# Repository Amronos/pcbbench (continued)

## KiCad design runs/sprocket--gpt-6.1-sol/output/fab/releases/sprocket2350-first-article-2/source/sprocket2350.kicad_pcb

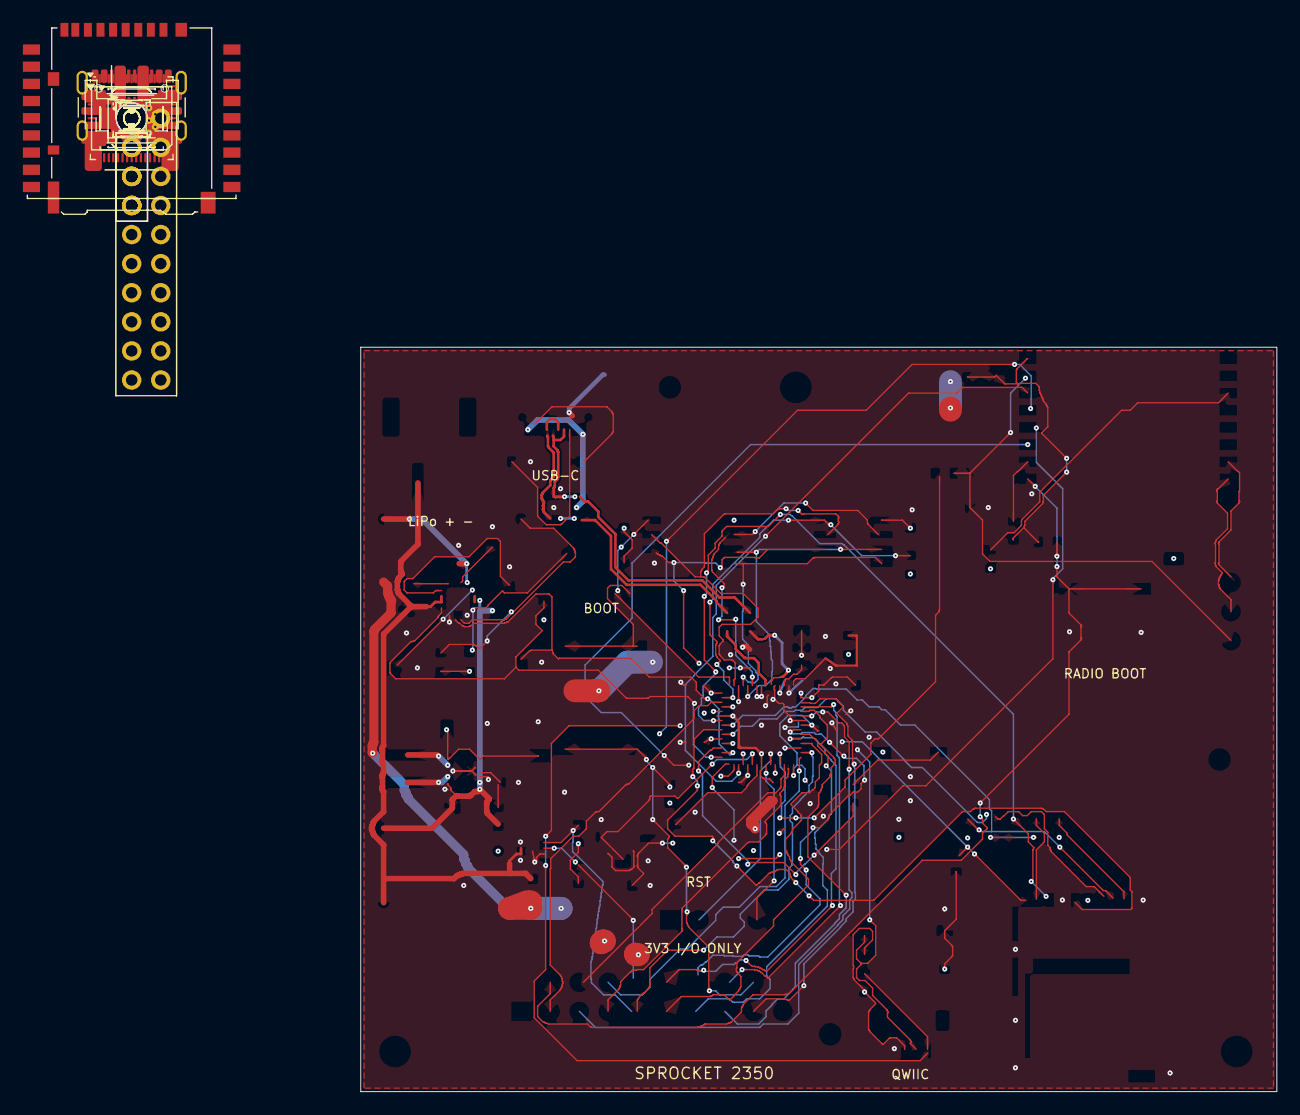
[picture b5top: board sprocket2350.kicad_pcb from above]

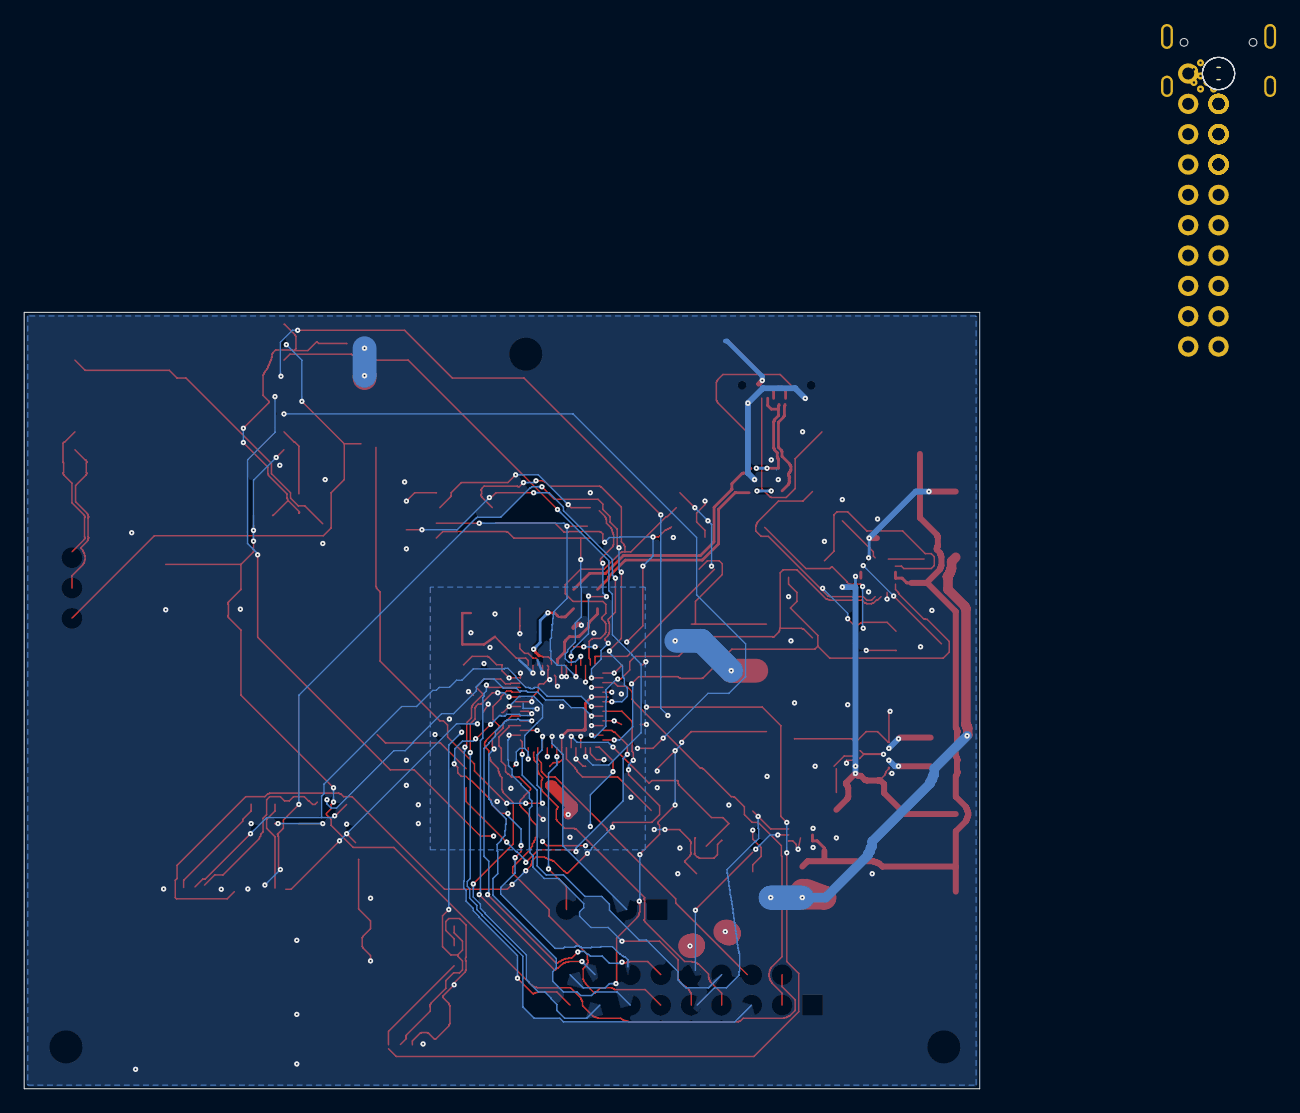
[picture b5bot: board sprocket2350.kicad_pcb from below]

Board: 4 copper layers, 80.0 x 65.0 mm, 106 parts (2 on the bottom side), 75 nets.

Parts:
C1, C2, C9, C10, C11, C12, C13, C14, C15, C16, C17, C18, C19, C25, C28, C31, C34, C35: 100 nF; C_0603_1608Metric
C3, C4: 15 pF; C_0603_1608Metric
C5, C7, C8: 4.7 µF; C_0805_2012Metric
C6: 22 µF; C_0603_1608Metric
C20: 100 nF; C_0201_0603Metric
C21, C29: 1 µF; C_0603_1608Metric
C22, C23, C24, C30, C33: 10 µF; C_0805_2012Metric
C26, C27, C32: 22 µF; C_1206_3216Metric
D1: RGB V6; LED_WS2812B_PLCC4_5.0x5.0mm_P3.2mm
FID1, FID2, FID3: Fiducial; Fiducial_1mm_Mask2mm
H1, H2, H3: M2.5; MountingHole_2.7mm_M2.5
J1: USB-C; USB_C_Receptacle_GCT_USB4105-xx-A_16P_TopMnt_Horizontal
J2: LiPo; JST_PH_S2B-PH-SM4-TB_1x02-1MP_P2.00mm_Horizontal
J3: Radio UART; PinHeader_1x04_P2.54mm_Vertical
J4: microSD; microSD_HC_Hirose_DM3AT-SF-PEJM5
J5: Qwiic / STEMMA QT; JST_SH_BM04B-SRSS-TB_1x04-1MP_P1.00mm_Vertical
J6: GPIO; PinHeader_2x10_P2.54mm_Vertical
J7: SWD; PinHeader_1x04_P2.54mm_Vertical
L1: 3.3 µH; L_Abracon_AOTA-B201610S
L2: 2.2 µH; L_Coilcraft_XxL4020
R1, R4, R13, R16, R17, R18, R19, R23, R24, R25, R26, R27, R28, R29, R30, R31: 10 kΩ; R_0603_1608Metric
R2: 1.8 kΩ; R_0603_1608Metric
R3, R5, R35: 1 kΩ; R_0603_1608Metric
R6: 33 Ω; R_0603_1608Metric
R7, R8, R32, R33: 5.1 kΩ; R_0603_1608Metric
R9, R10: 27 Ω; R_0603_1608Metric
R11: 8.66 kΩ; R_0603_1608Metric
R12: 3.48 kΩ; R_0603_1608Metric
R14: 68.1 kΩ; R_0603_1608Metric
R20, R21: 3.3 kΩ; R_0603_1608Metric
R22: 100 kΩ; R_0603_1608Metric
R34: 330 Ω; R_0603_1608Metric
R36: 100 Ω; R_0603_1608Metric
SW1: BOOT; SW_SPST_TL3342
SW2: RESET; SW_SPST_TL3342
SW3: RADIO BOOT; SW_SPST_TL3342
TP1: VBUS; TestPoint_Pad_D1.0mm
TP2: SYS; TestPoint_Pad_D1.0mm
TP3: +3V3; TestPoint_Pad_D1.0mm
TP4: GND; TestPoint_Pad_D1.0mm
TP5: BAT; TestPoint_Pad_D1.0mm
TP6: CHG_N; TestPoint_Pad_D1.0mm
TP7: USB_PGOOD_N; TestPoint_Pad_D1.0mm
TP8: CORE_1V1; TestPoint_Pad_D1.0mm
U1: RP2350A; QFN-60-1EP_7x7mm_P0.4mm_EP3.4x3.4mm
U2: 16 MB flash; SOIC-8_5.3x5.3mm_P1.27mm
U3: 8 MB PSRAM; SOIC-8_3.9x4.9mm_P1.27mm
U4: USB ESD; SOT-23-6
U5: Power-path charger; VQFN-16-1EP_3x3mm_P0.5mm_EP1.6x1.6mm
U6: 3.3 V buck-boost; Texas_DRC0010J
U7: Wi-Fi + BLE; ESP32-C3-WROOM-02
U8: Battery voltage / SOC; TDFN-8-1EP_2x2mm_P0.5mm_EP0.8x1.2mm
Y1: 12 MHz; Crystal_SMD_3225-4Pin_3.2x2.5mm

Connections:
/+3V3: C1.1, C2.1, C6.1, C9.1, C10.1, C11.1, C12.1, C13.1, C14.1, C15.1, C16.1, C17.1, C26.1, C27.1, C30.1, C31.1, C32.1, C33.1, C34.1, C35.1, D1.1 (VDD), J4.4 (VDD), J5.2, J6.1, J6.19, J7.1, R1.1, R2.1, R4.1, R6.1, R17.1, R18.1, R19.1, R20.1, R21.1, R23.1, R24.1, R25.1, R26.1, R27.1, R28.1, R29.1, R30.1, R31.1, R32.1, R33.1, TP3.1 (1_1), U1.1 (IOVDD), U1.11 (IOVDD), U1.20 (IOVDD), U1.30 (IOVDD), U1.38 (IOVDD), U1.44 (ADC_AVDD), U1.45 (IOVDD), U1.49 (VREG_VIN), U1.53 (USB_OTP_VDD), U1.54 (QSPI_IOVDD), U2.8 (VCC), U3.8 (VDD), U6.1 (VOUT), U6.10 (FB), U7.1 (3V3)
/ADC0: J6.5, U1.40 (GPIO26/ADC0)
/ADC1: J6.15, U1.41 (GPIO27/ADC1)
/ADC2: J6.16, U1.42 (GPIO28/ADC2)
/ADC3: J6.17, U1.43 (GPIO29/ADC3)
/BAT: C22.1, C28.1, J2.2, TP5.1 (1_1), U5.2 (BAT), U5.3 (BAT), U8.2 (CELL), U8.3 (VDD)
/BAT_TS: R13.1, U5.1 (TS)
/BOOT_SWITCH: R3.2, SW1.1
/BUCK_L1: L2.1, U6.4 (L1)
/BUCK_L2: L2.2, U6.2 (L2)
/BUCK_VINA: C25.1, R36.2, U6.8 (VINA)
/CC1: J1.A5 (CC1), R7.1
/CC2: J1.B5 (CC2), R8.1
/CHARGE_DISABLE: R17.2, U1.15 (GPIO11), U5.4 (~CE)
/CHG_ILIM: R12.1, U5.12 (ILIM)
/CHG_ISET: R11.1, U5.16 (ISET)
/CHG_N: R19.2, TP6.1 (1_1), U5.9 (~CHG)
/CHG_TMR: R14.1, U5.14 (TMR)
/CORE_1V1: C7.1, C8.1, C18.1, C19.1, C20.1, L1.1, TP8.1 (1_1), U1.6 (DVDD), U1.23 (DVDD), U1.39 (DVDD), U1.50 (VREG_FB)
/FLASH_CS: R1.2, R3.1, U1.60 (~QSPI_SS), U2.1 (~CS)
/GAUGE_SCL: J6.10, R21.2, U1.33 (GPIO21), U8.7 (SCL)
/GAUGE_SDA: J6.9, R20.2, U1.32 (GPIO20), U8.8 (SDA)
/GND: C1.2, C2.2, C3.2, C4.2, C5.2, C6.2, C7.2, C8.2, C9.2, C10.2, C11.2, C12.2, C13.2, C14.2, C15.2, C16.2, C17.2, C18.2, C19.2, C20.2, C21.2, C22.2, C23.2, C24.2, C25.2, C26.2, C27.2, C28.2, C29.2, C30.2, C31.2, C32.2, C33.2, C34.2, C35.2, D1.3 (VSS), J1.A1 (GND), J1.A12 (GND), J1.B1 (GND), J1.B12 (GND), J1.SH (SHIELD), J2.1, J3.1, J4.6 (VSS), J4.10 (DET_A), J4.SH (SHIELD), J5.1, J6.2, J6.20, J7.3, R7.2, R8.2, R11.2, R12.2, R13.2, R14.2, R16.2, R22.2, SW1.2, SW2.2, SW3.2, TP4.1 (1_1), U1.47 (VREG_PGND), U1.61 (GND), U2.4 (GND), U3.4 (VSS), U4.2 (GND), U5.5 (EN2), U5.8 (VSS), U5.17 (VSS), U6.3 (PGND), U6.7 (PS/SYNC), U6.9 (GND), U6.11 (PGND), U7.9 (GND), U7.19 (GND), U8.1 (CTG), U8.4 (GND), U8.6 (QSTRT), U8.9 (EP), Y1.2 (G), Y1.4 (G)
/GPIO1: J6.3, U1.3 (GPIO1)
/GPIO17: J6.6, U1.28 (GPIO17)
/GPIO18: J6.7, U1.29 (GPIO18)
/GPIO19: J6.8, U1.31 (GPIO19)
/GPIO22: J6.11, U1.34 (GPIO22)
/GPIO23: J6.12, U1.35 (GPIO23)
/GPIO24: J6.13, U1.36 (GPIO24)
/GPIO25: J6.14, U1.37 (GPIO25)
/I2C_SCL: J5.4, R33.2, U1.5 (GPIO3)
/I2C_SDA: J5.3, R32.2, U1.4 (GPIO2)
/MCU_USB_N: R10.2, U1.51 (USB_DM)
/MCU_USB_P: R9.2, U1.52 (USB_DP)
/PROG_RX: J3.3, U7.11 (IO20/RXD)
/PROG_TX: J3.2, U7.12 (IO21/TXD)
/PSRAM_CS: R2.2, U1.2 (GPIO0), U3.1 (~CE)
/QSPI_CLK: U1.56 (QSPI_SCLK), U2.6 (CLK), U3.6 (SCLK)
/QSPI_D0: U1.57 (QSPI_SD0), U2.5 (DI/IO_{0}), U3.5 (SI/SIO0)
/QSPI_D1: U1.59 (QSPI_SD1), U2.2 (DO/IO_{1}), U3.2 (SO/SIO1)
/QSPI_D2: U1.58 (QSPI_SD2), U2.3 (~WP/IO_{2}), U3.3 (SIO2)
/QSPI_D3: U1.55 (QSPI_SD3), U2.7 (~HOLD/~RESET/IO_{3}), U3.7 (SIO3)
/RADIO_BOOT: J6.4, R24.2, SW3.1, U7.8 (IO9)
/RADIO_CTRL: R35.1, U1.27 (GPIO16)
/RADIO_EN: C29.1, J3.4, R22.1, R35.2, U7.2 (EN)
/RADIO_IO2: R25.2, U7.16 (IO2)
/RADIO_IO8: R23.2, U7.7 (IO8)
/RGB_DATA: R34.1, U1.13 (GPIO9)
/RGB_DIN: D1.4 (DIN), R34.2
/RUN: J6.18, R4.2, SW2.1, U1.26 (RUN)
/SD_CLK: J4.5 (CLK), U1.9 (GPIO6)
/SD_CS: J4.2 (DAT3/CD), R26.2, U1.8 (GPIO5)
/SD_DAT1: J4.8 (DAT1), R29.2
/SD_DAT2: J4.1 (DAT2), R30.2
/SD_DETECT: J4.9 (DET_B), R31.2, U1.12 (GPIO8)
/SD_MISO: J4.7 (DAT0), R28.2, U1.7 (GPIO4)
/SD_MOSI: J4.3 (CMD), R27.2, U1.10 (GPIO7)
/SWCLK: J7.4, U1.24 (SWCLK)
/SWDIO: J7.2, U1.25 (SWDIO)
/SYS: C23.1, C24.1, R36.1, TP2.1 (1_1), U5.10 (OUT), U5.11 (OUT), U6.5 (VIN), U6.6 (EN)
/UART_CTS: U1.18 (GPIO14), U7.3 (IO4)
/UART_RTS: U1.19 (GPIO15), U7.4 (IO5)
/UART_RX: U1.17 (GPIO13), U7.6 (IO7)
/UART_TX: U1.16 (GPIO12), U7.5 (IO6)
/USB_500_EN: R16.1, U1.14 (GPIO10), U5.6 (EN1)
/USB_D_N: J1.A7 (D-), J1.B7 (D-), R10.1, U4.1 (I/O1), U4.6 (I/O1)
/USB_D_P: J1.A6 (D+), J1.B6 (D+), R9.1, U4.3 (I/O2), U4.4 (I/O2)
/USB_PGOOD_N: R18.2, TP7.1 (1_1), U5.7 (~PGOOD)
/VBUS: C21.1, J1.A4 (VBUS), J1.A9 (VBUS), J1.B4 (VBUS), J1.B9 (VBUS), TP1.1 (1_1), U4.5 (VBUS), U5.13 (IN)
/VREG_AVDD: C5.1, R6.2, U1.46 (VREG_AVDD)
/VREG_LX: L1.2, U1.48 (VREG_LX)
/XIN: C3.1, U1.21 (XIN), Y1.1
/XOUT: R5.1, U1.22 (XOUT)
/XTAL_OUT: C4.1, R5.2, Y1.3

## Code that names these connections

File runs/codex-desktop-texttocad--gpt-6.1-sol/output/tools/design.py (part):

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

gpio = {
    0: 'PSRAM_CS', 1: 'GPIO1', 2: 'GPIO2', 3: 'GPIO3', 4: 'I2C_SDA', 5: 'I2C_SCL',
    6: 'GPIO6', 7: 'GPIO7', 8: 'GPIO8', 9: 'GPIO9', 10: 'SD_CLK', 11: 'SD_MOSI',
    12: 'SD_MISO', 13: 'SD_CS', 14: 'RGB_DATA', 15: 'SD_DETECT', 16: 'USB_500_EN',
    17: 'USB_SUSPEND_EN', 18: 'ESP_EN_CTRL', 19: 'ESP_BOOT_CTRL', 20: 'WIFI_TX', 21: 'WIFI_RX',
    22: 'WIFI_CTS', 23: 'WIFI_RTS', 24: 'CHARGE_N', 25: 'POWERGOOD_N',
    26: 'BAT_ADC', 27: 'VBUS_ADC', 28: 'GPIO28_ADC2', 29: 'GPIO29_ADC3'
}
rp_nets = {1: '+3V3', 6: '+1V1', 11: '+3V3', 20: '+3V3', 21: 'XIN',
           22: 'XOUT', 23: '+1V1', 24: 'SWCLK', 25: 'SWDIO', 26: 'RUN',
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    (76, 38, 90), 'Interfaces', (295, 62, 0),
    'Connector_JST:JST_SH_SM04B-SRSS-TB_1x04-1MP_P1.00mm_Horizontal',
    '3.3V I2C, pin1 GND, pin2 VCC, pin3 SDA, pin4 SCL')
header_nets = {1: '+3V3', 2: 'GND', 3: 'GPIO1', 4: 'GPIO2', 5: 'GPIO3', 6: 'GPIO6',
               7: 'GPIO7', 8: 'GPIO8', 9: 'GPIO9', 10: 'CHARGE_N', 11: 'POWERGOOD_N',
               12: 'RGB_DATA', 13: 'GPIO28_ADC2', 14: 'GPIO29_ADC3', 15: 'I2C_SDA',
               16: 'I2C_SCL', 17: 'RUN', 18: 'GND', 19: 'VBUS', 20: 'VSYS'}
add('J5', 'Connector_Generic', 'Conn_02x10_Odd_Even', 'GPIO expansion',
    'TSW-110-07-G-D', 'Samtec', header_nets, (48, 49, 0), 'MCU', (240, 165, 0),
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
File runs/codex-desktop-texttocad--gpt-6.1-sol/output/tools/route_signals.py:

from pathlib import Path
import sys
from cad import kicad_pcb
from cad.kicad import route

ROOT = Path(__file__).resolve().parents[1]
GROUPS = {
    'memory': ['QSPI_CLK_SRC', 'QSPI_CLK', 'QSPI_IO0', 'QSPI_IO1', 'QSPI_IO2', 'QSPI_IO3', 'FLASH_CS', 'PSRAM_CS'],
    'analog': ['MAIN_FB', 'MAIN_VAUX', 'CORE_FB', 'ADC_AVDD', 'BAT_SENSE', 'BAT_BUF', 'BAT_ADC', 'BAT_TS', 'CHG_ISET', 'CHG_ILIM', 'VBUS_ADC'],
    'power': ['+1V1', '+3V3', 'VSYS', 'VBAT', 'VBUS', 'VBUS_RAW', 'MAIN_PG', 'PWR_EN', 'PWR_SWITCH'],
    'interfaces': ['USB_CC1', 'USB_CC2', 'SD_CLK', 'SD_MOSI', 'SD_MISO', 'SD_CS', 'SD_DAT1', 'SD_DAT2', 'SD_DETECT', 'I2C_SDA', 'I2C_SCL', 'RGB_DATA', 'RGB_DIN'],
    'wireless': ['WIFI_TX', 'WIFI_RX', 'WIFI_CTS', 'WIFI_RTS', 'ESP_EN', 'ESP_BOOT', 'ESP_EN_CTRL', 'ESP_BOOT_CTRL', 'ESP_STRAP2', 'ESP_STRAP8', 'ESP_PROG_TX', 'ESP_PROG_RX'],
    'control': ['RUN', 'BOOT_SWITCH', 'SWCLK', 'SWDIO', 'CHARGE_N', 'POWERGOOD_N', 'USB_500_EN', 'USB_SUSPEND_EN', 'GPIO1', 'GPIO2', 'GPIO3', 'GPIO6', 'GPIO7', 'GPIO8', 'GPIO9', 'GPIO28_ADC2', 'GPIO29_ADC3'],
}

with kicad_pcb.edit(str(ROOT / 'Atlas2350.kicad_pcb')) as board:
    available = {net.name for net in board.get_nets()}
    group = sys.argv[1]
    entries = []
    for net in GROUPS[group]:
        if net not in available:
            continue
        width = 0.3 if net in {'+3V3', '+1V1', 'VSYS', 'VBAT', 'VBUS', 'VBUS_RAW'} else 0.15
        entries.append({'net': net, 'layers': ['F.Cu', 'B.Cu'], 'width': width})
    result = route(board, entries, layers=['F.Cu', 'B.Cu'], via_cost=2)
    print('\n'.join(result.human_lines()))
    board.refill_zones()

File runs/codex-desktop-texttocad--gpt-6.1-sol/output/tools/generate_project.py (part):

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    }
    annotations = {
        'MCU': [('150MHz nominal. External LDO supplies DVDD: VREG_FB=GND, LX=NC.\nKeep VREG_VIN and VREG_AVDD powered. Set VREG.HIZ=1 in firmware; never select low-power VREG mode.', 25, 20),
                ('IOs are 3.3V, not 5V tolerant. No SWO.\nExpansion pin19 VBUS and pin20 VSYS are outputs only: never back-power.', 230, 227)],
        'Memory': [('QSPI bus shared; CS0 is flash, GP0 is PSRAM CS1. Both chip selects pulled high.\n33R source termination on clock. Start QSPI <=31.25MHz; validate signal integrity on first articles.', 25, 20),
                   ('BOOTSEL: hold SW2, pulse RUN (SW1), release SW2 after USB enumerates.\n1k limits current if BOOTSEL is pressed while the flash chip-select output is active.', 210, 162)],
        'Power': [('USB_500_EN=0 at reset: 100mA USB mode. Set to1 only after a 500mA USB grant.\nCharger ISET=3.57k: 250mA nominal. ITERM=NC: 10% termination; TMR=NC: 5h safety timer.', 25, 20),
                  ('BATTERY: protected 1S LiPo, >=500mAh, 4.2V charging; 10k NTC required.\nJ2 pins 1=BAT+, 2=GND, 3=NTC. THIS IS A CUSTOM 3-PIN PINOUT.\nNo battery supplied or soldered. Missing NTC inhibits charging.', 25, 225),
                  ('VBAT approximately 2 * BAT_ADC; divider buffered by U9.\nVBUS_ADC is presence detection, not precision voltage measurement.\nUSB_500_EN / USB_SUSPEND_EN: 00=100mA,10=500mA,11=suspend.', 235, 210)],
        'Interfaces': [('USB2.0 device / 5V sink only; no PD, no host power sourcing.\nBoth CC pins use separate 5.1k Rd. ESD array sits at the receptacle; 27R series resistors at U1.', 25, 20),
                       ('RGB V6 only: VIH=0.55*VDD; U10 switches VSYS with PWR_EN.\nBlank RGB below VBAT about3.6V under load; limit current to15mA.\nRGB not guaranteed when LED_VDD<3.3V. I2C 3.3V/4.7k; SD SPI initially<=12.5MHz.', 258, 245)],
        'Wireless': [('ESP-AT UART1: GPIO6 RX <- RP GP20; GPIO7 TX -> RP GP21.\nGPIO4 RTS -> RP GP22 CTS; GPIO5 CTS <- RP GP23 RTS.\nUART0 GPIO20/21 is a separate 3.3V programming interface; start115200baud.', 25, 20),
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    }
    for page, (sheet_name, description) in enumerate(descriptions.items(), 2):
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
